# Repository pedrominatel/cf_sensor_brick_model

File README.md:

# Internet of Things Sensor Brick (Base Project)

This is the series of sensors for IoT projects, made on base of the famous brick game. This is compatible to the format to be used with others bricks to prototype quickly.

This is the base project using the Bosch BMI160.

Sensor | Project Link
------------ | -------------
Bosch BMI160 | [Goto Project](https://github.com/pedrominatel/cf_sensor_brick_model)
Bosch BME680 | Soon
Texas HDC1080 | Soon

Happy Hacking!

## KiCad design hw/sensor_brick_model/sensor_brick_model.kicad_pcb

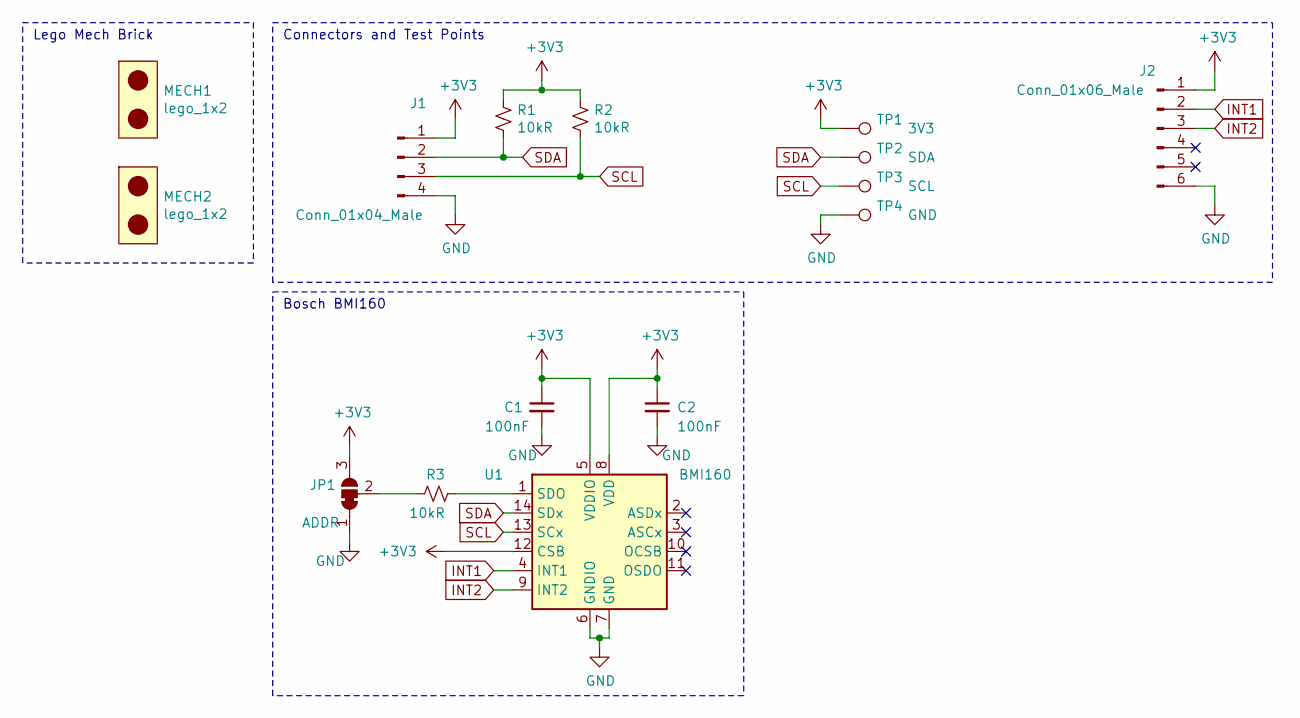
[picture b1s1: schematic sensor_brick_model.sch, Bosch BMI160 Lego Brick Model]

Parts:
C1, C2: 100nF; C_0603_1608Metric
J1: Conn_01x04_Male; PinHeader_1x04_P2.00mm_Vertical
J2: Conn_01x06_Male; PinHeader_1x06_P2.00mm_Vertical
JP1: ADDR; SolderJumper-3_P1.3mm_Bridged12_RoundedPad1.0x1.5mm
MECH1, MECH2: lego_1x2
R1, R2, R3: 10kR; R_0603_1608Metric
TP1: 3V3; TestPoint_Pad_D2.5mm
TP2: SDA; TestPoint_Pad_D2.5mm
TP3: SCL; TestPoint_Pad_D2.5mm
TP4: GND; TestPoint_Pad_D2.5mm
U1: BMI160; Bosch_LGA-14_3x2.5mm_P0.5mm

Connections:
+3V3: C1.1, C2.1, J1.1, J2.1, JP1.3 (B), R1.1, R2.1, TP1.1, U1.5 (VDDIO), U1.8 (VDD), U1.12 (CSB)
GND: C1.2, C2.2, J1.4, J2.6, JP1.1 (A), TP4.1, U1.6 (GNDIO), U1.7 (GND)
INT1: J2.2, U1.4 (INT1)
INT2: J2.3, U1.9 (INT2)
unnamed: JP1.2 (C), R3.1
unnamed: R3.2, U1.1 (SDO)
SCL: J1.3, R2.2, TP3.1, U1.13 (SCx)
SDA: J1.2, R1.2, TP2.1, U1.14 (SDx)

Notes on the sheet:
Bosch BMI160
Lego Mech Brick
Connectors and Test Points

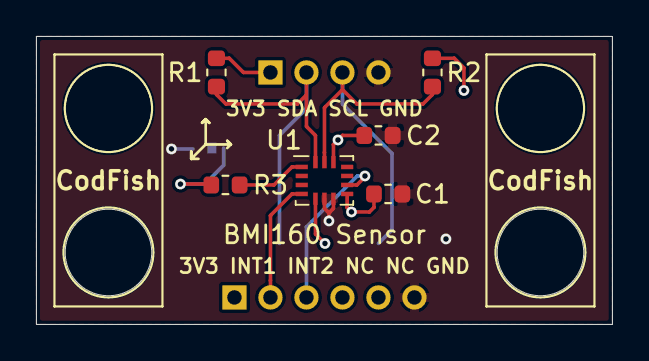
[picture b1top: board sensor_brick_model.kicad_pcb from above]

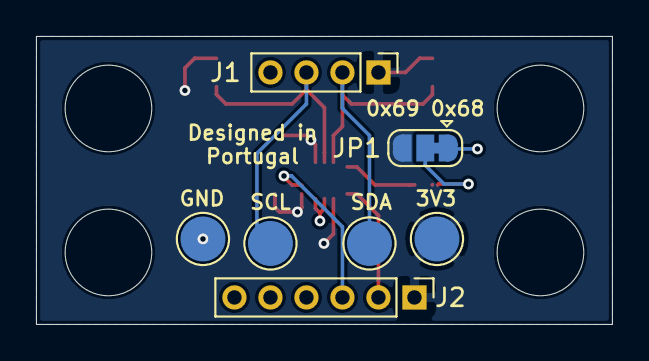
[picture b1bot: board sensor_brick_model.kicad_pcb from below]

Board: 2 copper layers, 32.0 x 16.0 mm, 15 parts (7 on the bottom side), 8 nets.

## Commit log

2020-10-10 Project added
2020-10-17 Version 1A done
